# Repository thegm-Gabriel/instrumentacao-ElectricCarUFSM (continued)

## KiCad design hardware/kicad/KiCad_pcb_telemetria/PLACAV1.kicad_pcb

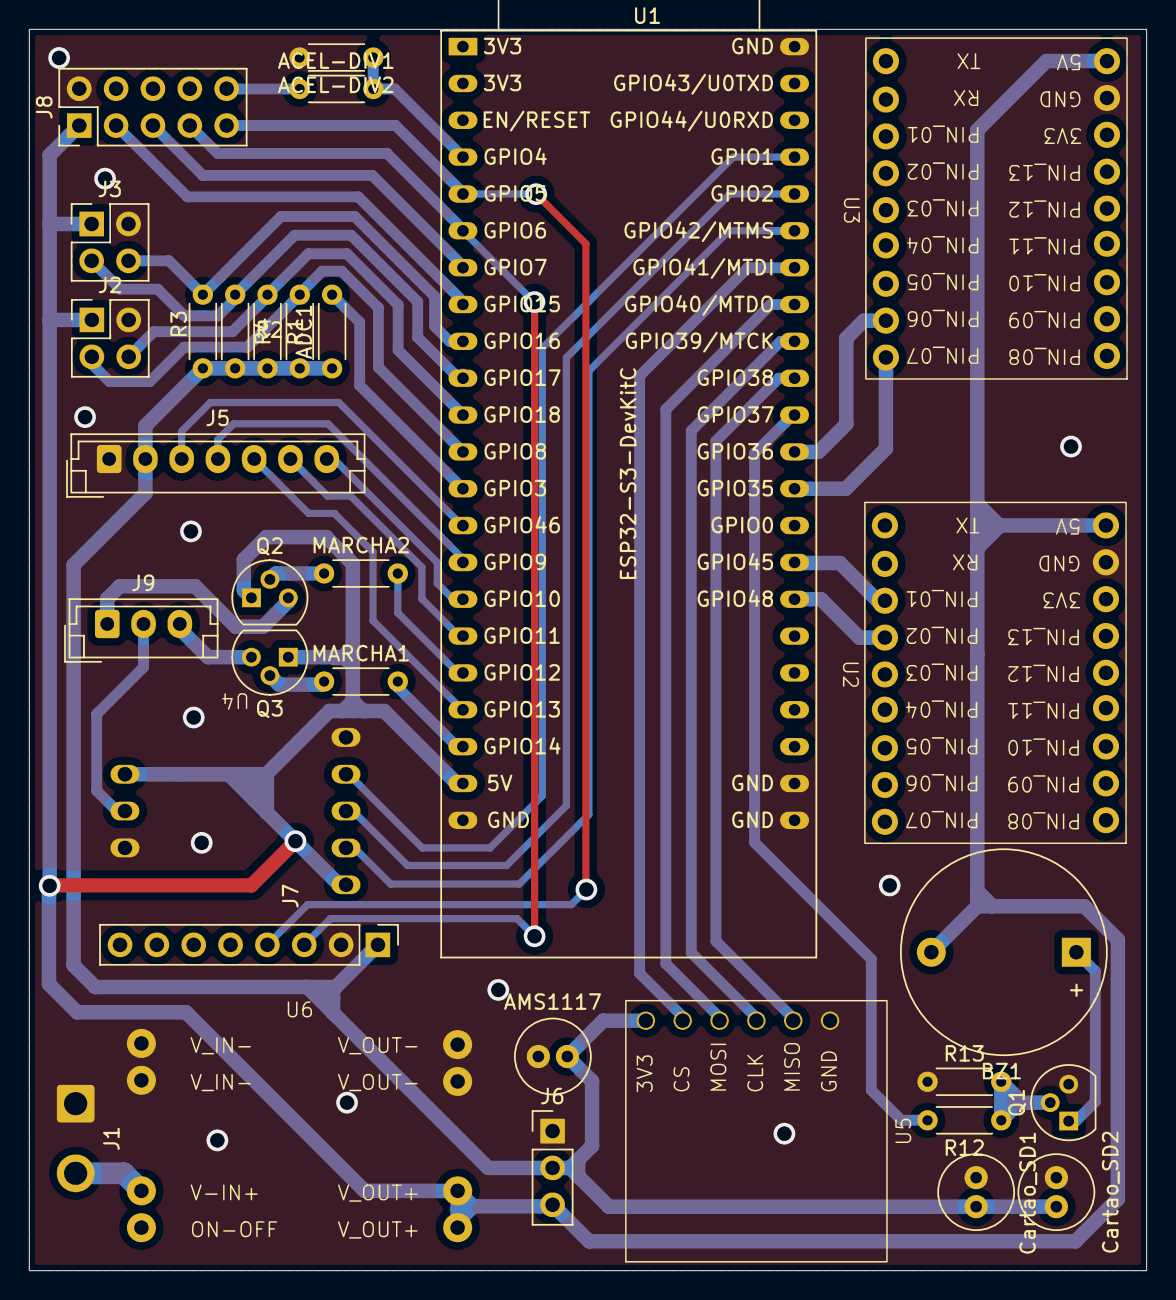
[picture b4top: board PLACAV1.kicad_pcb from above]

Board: 2 copper layers, 77.0 x 85.6 mm, 32 parts (0 on the bottom side), 41 nets.

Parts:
ACEL-DIV1, ACEL-DIV2: 10k; R_Axial_DIN0204_L3.6mm_D1.6mm_P5.08mm_Horizontal
ADC1: 10k; R_Axial_DIN0204_L3.6mm_D1.6mm_P5.08mm_Horizontal
AMS1117: 10uF; C_Radial_D5.0mm_H11.0mm_P2.00mm
BZ1: Buzzer; Buzzer_D14mm_H7mm_P10mm
Cartao_SD1: 100nF; C_Radial_D5.0mm_H11.0mm_P2.00mm
Cartao_SD2: 100uF; C_Radial_D5.0mm_H11.0mm_P2.00mm
J1: ALIMENTACAO_48V; SolderWire-0.75sqmm_1x02_P4.8mm_D1.25mm_OD2.3mm
J2, J3: Conn_02x02_Odd_Even; PinHeader_2x02_P2.54mm_Vertical
J5: INDICADOR; JST_EH_B7B-EH-A_1x07_P2.50mm_Vertical
J6: AMS1117; PinHeader_1x03_P2.54mm_Vertical
J7: Acelerometro; PinHeader_1x08_P2.54mm_Vertical
J8: Conn_02x05_Odd_Even; PinHeader_2x05_P2.54mm_Vertical
J9: DRIVER; JST_EH_B3B-EH-A_1x03_P2.50mm_Vertical
MARCHA1, MARCHA2: 1k; R_Axial_DIN0204_L3.6mm_D1.6mm_P5.08mm_Horizontal
Q1, Q2, Q3: BC337; TO-92
R1, R2, R3, R4: 4.7k; R_Axial_DIN0204_L3.6mm_D1.6mm_P5.08mm_Horizontal
R12: 1k; R_Axial_DIN0204_L3.6mm_D1.6mm_P5.08mm_Horizontal
R13: 10K; R_Axial_DIN0204_L3.6mm_D1.6mm_P5.08mm_Horizontal
U1: ESP32-S3-DevKitC
U2: ESP32S3-SUPERMINI - VISITANTES; ESP32-S3-SuperMini
U3: ESP32S3-SUPERMINI - TIME; ESP32-S3-SuperMini
U4: X9C103S
U5: CartãoSD-MODULO
U6: ConversorBUCK_100V_5V-2A

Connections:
+3V3: ADC1.1, AMS1117.2, Cartao_SD1.2, Cartao_SD2.2, J5.2, J6.2, J7.1, R1.2, R2.2, R3.2, R4.2, U5.1 (3V3)
+5V: BZ1.2 (-), J2.1, J3.1, J6.3, J8.1, Q2.1 (C), Q3.1 (C), U1.21 (5V), U2.1 (5V), U3.1 (5V), U4.5 (VCC), U4.6 (VH), U6.3 (V_OUT+)
CS: U1.39 (GPIO42/MTMS), U4.4 (CS)
GND: ACEL-DIV2.2, AMS1117.1, Cartao_SD1.1, Cartao_SD2.1, J1.1, J2.2, J3.2, J5.1, J6.1, J7.2, J8.2, Q1.3 (E), R13.1, U1.22 (GND), U1.23 (GND), U1.24 (GND), U1.44 (GND), U2.2 (GND), U3.2 (GND), U4.1 (GND), U4.8 (VL), U5.6 (GND), U6.2 (V_IN-), U6.4 (V_OUT-)
INC: U1.40 (GPIO2/ADC1_CH1), U4.3 (INC)
MARCHA-A: J8.3, U1.8 (GPIO15/ADC2_CH4/32K_P)
MARCHA-A-OUT: MARCHA1.2, U1.20 (GPIO14/ADC2_CH3)
MARCHA-A-conector: J9.3, Q3.3 (E)
MARCHA-B: J8.5, U1.7 (GPIO7/ADC1_CH6)
MARCHA-B-OUT: MARCHA2.2, U1.18 (GPIO12/ADC2_CH1)
MARCHA-B-conector: J9.1, Q2.3 (E)
unnamed: BZ1.1 (+), Q1.1 (C)
unnamed: J1.2, U6.1 (V_IN+)
unnamed: J9.2, U4.7 (W)
unnamed: Q1.2 (B), R12.1, R13.2
unnamed: MARCHA2.1, Q2.2 (B)
unnamed: MARCHA1.1, Q3.2 (B)
S3MESTRE-GPIO4-ENCODER01_A: J3.4, R3.1, U1.9 (GPIO16/ADC2_CH5/32K_N)
S3MESTRE-GPIO5-ENCODER01_B: J3.3, R4.1, U1.10 (GPIO17/ADC2_CH6)
S3MESTRE-GPIO6-ENCODER02_A: J2.4, R1.1, U1.11 (GPIO18/ADC2_CH7)
S3MESTRE-GPIO7-ENCODER02_B: J2.3, R2.1, U1.12 (GPIO8/ADC1_CH7)
S3MESTRE-GPIO8-I2C_SDA: J7.4, J8.9, U1.5 (GPIO5/ADC1_CH4)
S3MESTRE-GPIO9: ADC1.2, U1.13 (GPIO3/ADC1_CH2)
S3MESTRE-GPIO9-I2C_SCL: J7.3, J8.7, U1.6 (GPIO6/ADC1_CH5)
S3MESTRE-GPIO10-LED_VERDE: J5.6, U1.17 (GPIO11/ADC2_CH0)
S3MESTRE-GPIO12-LED_VERMELHO: J5.7, U1.16 (GPIO10/ADC1_CH9)
S3MESTRE-GPIO13-LED_AZUL: J5.5, U1.19 (GPIO13/ADC2_CH2)
S3MESTRE-GPIO14-BUZZER: R12.2, U1.34 (GPIO37)
S3MESTRE-GPIO15-SD_CS: U1.38 (GPIO41/MTDI), U5.2 (CS)
S3MESTRE-GPIO16-SD_MOSI: U1.37 (GPIO40/MTDO), U5.3 (MOSI)
S3MESTRE-GPIO17-SD_SCK: U1.36 (GPIO39/MTCK), U5.4 (CLK)
S3MESTRE-GPIO18-SD_MISO: U1.35 (GPIO38), U5.5 (MISO)
S3MESTRE-GPIO39-TX_VISITANTES: U1.29 (GPIO48), U2.13 (PIN_02)
S3MESTRE-GPIO40-RX_VISITANTES: U1.30 (GPIO45), U2.12 (PIN_01)
S3MESTRE-GPIO41-TX_EQUIPE: U1.32 (GPIO35), U3.18 (PIN_07)
S3MESTRE-GPIO42-RX_EQUIPE: U1.33 (GPIO36), U3.17 (PIN_06)
S3MESTRE-I2C_SCL-TELA: J5.4, U1.15 (GPIO9/ADC1_CH8)
S3MESTRE-I2C_SDA-TELA: J5.3, U1.14 (GPIO46)
SGN_ACEL: ACEL-DIV1.2, ACEL-DIV2.1, U1.4 (GPIO4/ADC1_CH3)
SGN_ACEL_CONECTOR: ACEL-DIV1.1, J8.10
U/D: U1.41 (GPIO1/ADC1_CH0), U4.2 (U/D)
